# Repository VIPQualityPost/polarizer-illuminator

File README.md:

# Polarizer-Illuminator

A microscope illuminator that includes a liquid crystal display as a tunable polarizer. By polarizing the illuminator light, the reflected light can be filtered through a second polarizer (in this case the LCD) with specular reflections and glare removed, depending on the amount of polarization applied (based on bias across LCD). The illuminator is powered over USB PD and can be controlled via a PC for automated control in conjunctions with motorized XY stages and microscope camera. Firmware can be updated over same cable providing power thanks to DFU bootloader, just hold the button on the back and plug into a PC. 

| Non-polarized image | Polarized image |
| --- | --- |
|  |  |

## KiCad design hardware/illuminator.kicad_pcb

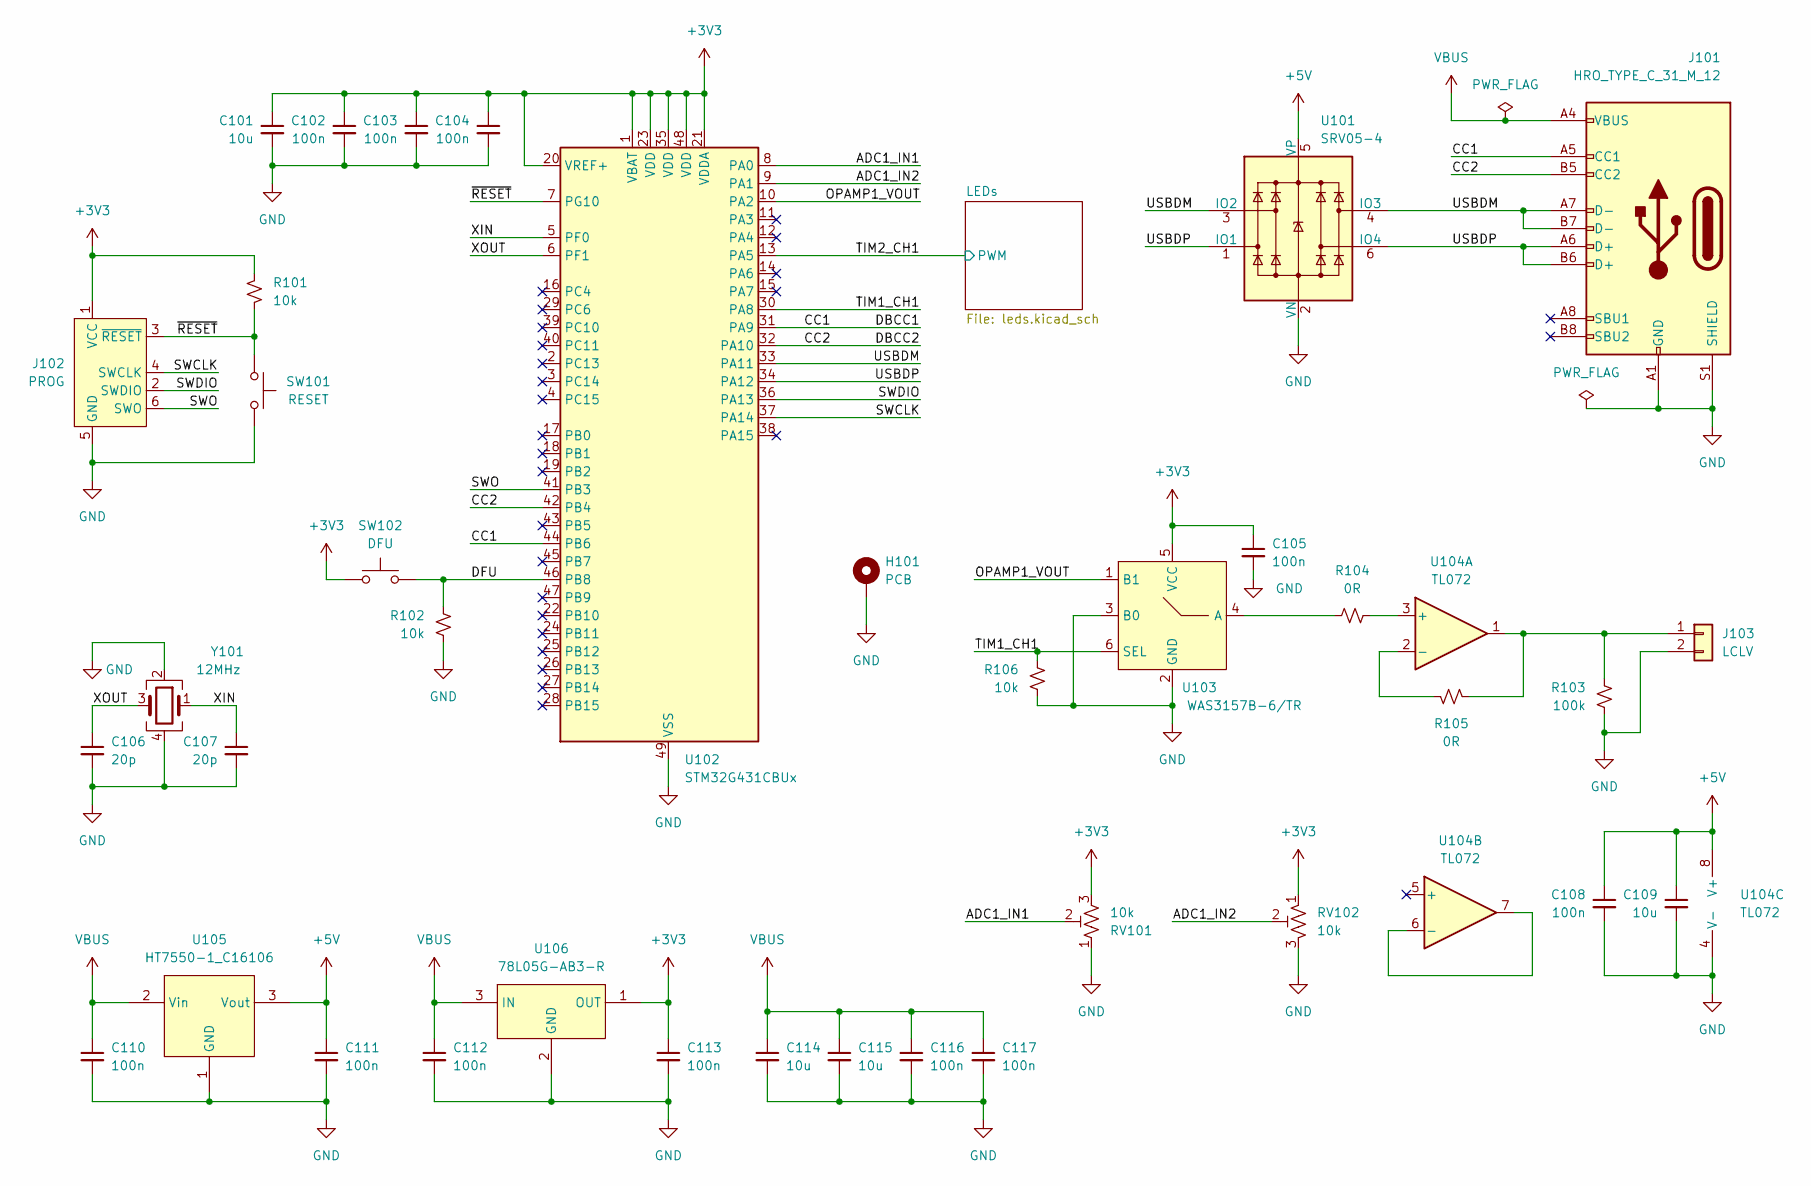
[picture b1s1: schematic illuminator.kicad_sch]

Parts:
C101, C109, C114, C115: 10u; C_0805_2012Metric; LCSC ID C440198
C102, C103, C104, C105, C108, C110, C111, C112, C113, C116, C117: 100n; C_0402_1005Metric; LCSC ID C307331
C106, C107: 20p; C_0402_1005Metric; LCSC ID C1554
H101: PCB; illuminator-monobody
J101: HRO_TYPE_C_31_M_12; USB_C_Receptacle_HRO_TYPE-C-31-M-12; LCSC ID C165948
J102: PROG; Tag-Connect_TC2030-IDC-NL_2x03_P1.27mm_Vertical
J103: LCLV; TestPoint_2Pads_Pitch5.08mm_Drill1.3mm
R101, R102, R106: 10k; R_0402_1005Metric; LCSC ID C25744
R103: 100k; R_0402_1005Metric; LCSC ID C25741
R104, R105: 0R; R_0402_1005Metric; LCSC ID C17168
RV101, RV102: 10k; RES-TH_RK09K1110A0J; LCSC ID C209767
SW101: RESET; PinHeader_1x02_P1.27mm_Vertical
SW102: DFU; KEY-TH_SKHHLWA010; LCSC ID C139764
U101: SRV05-4; SOT-23-6; LCSC ID C7420376
U102: STM32G431CBUx; QFN-48-1EP_7x7mm_P0.5mm_EP5.6x5.6mm; LCSC ID C529356
U103: WAS3157B-6/TR; SOT-363_L2.0-W1.3-P0.65-LS2.1-BL; LCSC ID C213161
U104: TL072; SOIC-8_3.9x4.9mm_P1.27mm; LCSC ID C6961
U105: HT7550-1_C16106; SOT-89-3; LCSC ID C16106
U106: 78L05G-AB3-R; SOT-89-3; LCSC ID C71136
Y101: 12MHz; Crystal_SMD_3225-4Pin_3.2x2.5mm; LCSC ID C9002

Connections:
+3V3: C101.1, C102.1, C103.1, C104.1, C105.1, C113.1, J102.1 (VCC), R101.1, RV101.3, RV102.1, SW102.1, U102.1 (VBAT), U102.20 (VREF+), U102.21 (VDDA), U102.23 (VDD), U102.35 (VDD), U102.48 (VDD), U103.5 (VCC), U106.1 (OUT)
+5V: C108.1, C109.1, C111.1, U101.5 (VP), U104.8 (V+), U105.3 (Vout)
/ADC1_IN1: RV101.2, U102.8 (PA0)
/ADC1_IN2: RV102.2, U102.9 (PA1)
/CC1: J101.A5 (CC1), U102.31 (PA9), U102.44 (PB6)
/CC2: J101.B5 (CC2), U102.32 (PA10), U102.42 (PB4)
/DFU: R102.1, SW102.2, U102.46 (PB8)
/OPAMP1_VOUT: U102.10 (PA2), U103.1 (B1)
/SWCLK: J102.4 (SWCLK), U102.37 (PA14)
/SWDIO: J102.2 (SWDIO), U102.36 (PA13)
/SWO: J102.6 (SWO), U102.41 (PB3)
/TIM1_CH1: R106.1, U102.30 (PA8), U103.6 (SEL)
/TIM2_CH1: U102.13 (PA5); also elsewhere on the board
/USBDM: J101.A7 (D-), J101.B7 (D-), U101.3 (IO2), U101.4 (IO3), U102.33 (PA11)
/USBDP: J101.A6 (D+), J101.B6 (D+), U101.1 (IO1), U101.6 (IO4), U102.34 (PA12)
/XIN: C107.1, U102.5 (PF0), Y101.1
/XOUT: C106.1, U102.6 (PF1), Y101.3
/~RESET: J102.3 (~RESET), R101.2, SW101.2, U102.7 (PG10)
GND: C101.2, C102.2, C103.2, C104.2, C105.2, C106.2, C107.2, C108.2, C109.2, C110.2, C111.2, C112.2, C113.2, C114.2, C115.2, C116.2, C117.2, H101.1, J101.A1 (GND), J101.A12 (GND), J101.B1 (GND), J101.B12 (GND), J101.S1 (SHIELD), J102.5 (GND), J103.2, R102.2, R103.2, R106.2, RV101.1, RV102.3, SW101.1, U101.2 (VN), U102.49 (VSS), U103.2 (GND), U103.3 (B0), U104.4 (V-), U105.1 (GND), U106.2 (GND), Y101.2, Y101.4; also elsewhere on the board
unnamed: J103.1, R103.1, R105.2, U104.1
unnamed: R104.1, U103.4 (A)
unnamed: R104.2, U104.3 (+)
unnamed: R105.1, U104.2 (-)
unnamed: U104.6 (-), U104.7
VBUS: C110.1, C112.1, C114.1, C115.1, C116.1, C117.1, J101.A4 (VBUS), J101.A9 (VBUS), J101.B4 (VBUS), J101.B9 (VBUS), U105.2 (Vin), U106.3 (IN); also elsewhere on the board

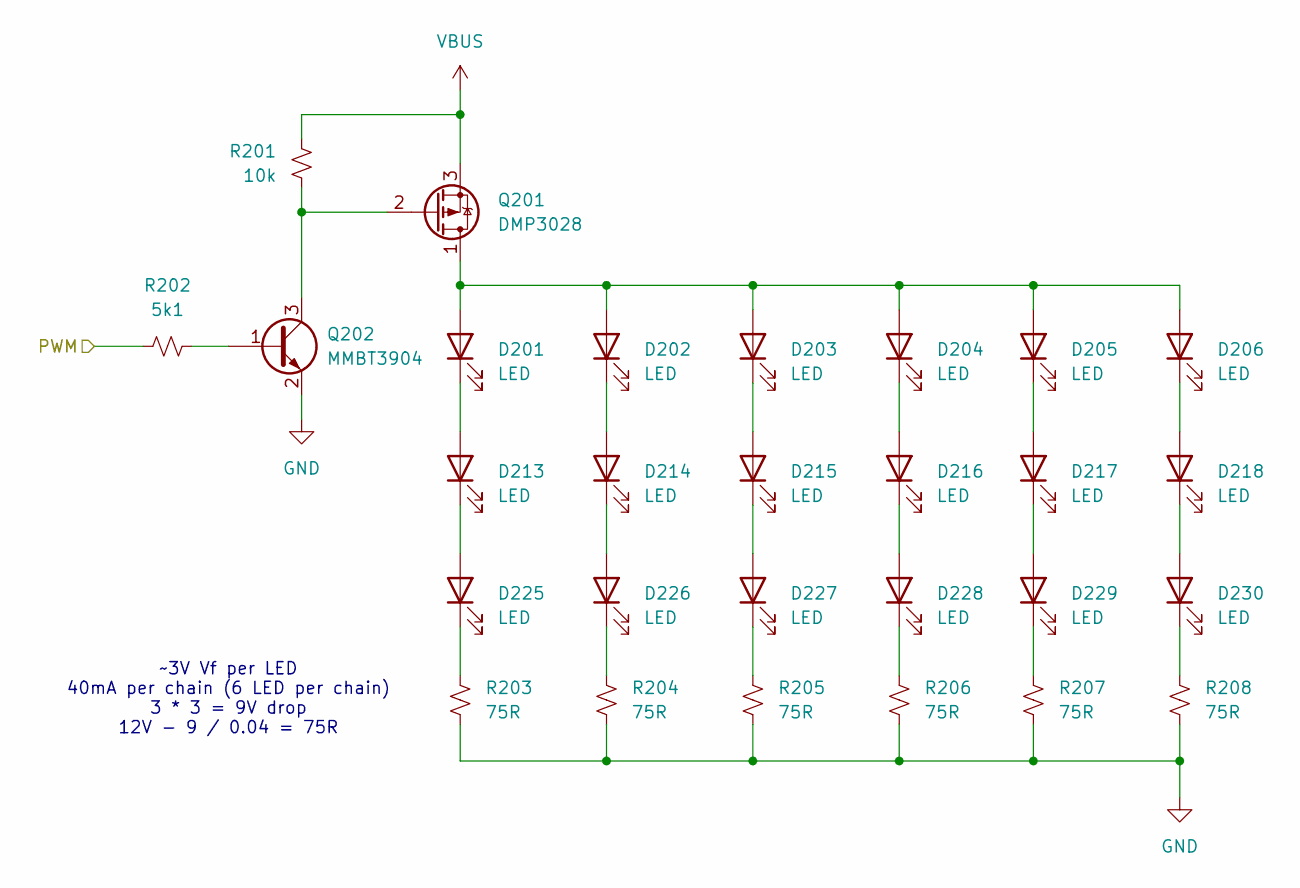
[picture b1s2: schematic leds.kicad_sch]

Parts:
D201, D202, D203, D204, D205, D206, D213, D214, D215, D216, D217, D218, D225, D226, D227, D228, D229, D230: LED; LED_PLCC_2835; LCSC ID C210312
Q201: DMP3028; DMP3028-UDFN2020; LCSC ID C150441
Q202: MMBT3904; SOT-23; LCSC ID C20526
R201: 10k; R_0402_1005Metric; LCSC ID C25744
R202: 5k1; R_0402_1005Metric; LCSC ID C25905
R203, R204, R205, R206, R207, R208: 75R; R_0805_2012Metric; LCSC ID C5198289

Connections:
/TIM2_CH1: R202.1; also elsewhere on the board
GND: Q202.2 (E), R203.2, R204.2, R205.2, R206.2, R207.2, R208.2; also elsewhere on the board
unnamed: D201.2 (A), D202.2 (A), D203.2 (A), D204.2 (A), D205.2 (A), D206.2 (A), Q201.1 (D)
unnamed: D201.1 (K), D213.2 (A)
unnamed: D202.1 (K), D214.2 (A)
unnamed: D203.1 (K), D215.2 (A)
unnamed: D204.1 (K), D216.2 (A)
unnamed: D205.1 (K), D217.2 (A)
unnamed: D206.1 (K), D218.2 (A)
unnamed: D213.1 (K), D225.2 (A)
unnamed: D214.1 (K), D226.2 (A)
unnamed: D215.1 (K), D227.2 (A)
unnamed: D216.1 (K), D228.2 (A)
unnamed: D217.1 (K), D229.2 (A)
unnamed: D218.1 (K), D230.2 (A)
unnamed: D225.1 (K), R203.1
unnamed: D226.1 (K), R204.1
unnamed: D227.1 (K), R205.1
unnamed: D228.1 (K), R206.1
unnamed: D229.1 (K), R207.1
unnamed: D230.1 (K), R208.1
unnamed: Q201.2 (G), Q202.3 (C), R201.2
unnamed: Q202.1 (B), R202.2
VBUS: Q201.3 (S), R201.1; also elsewhere on the board

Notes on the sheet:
~3V Vf per LED 40mA per chain (6 LED per chain) 3 * 3 = 9V drop 12V - 9 / 0.04 = 75R

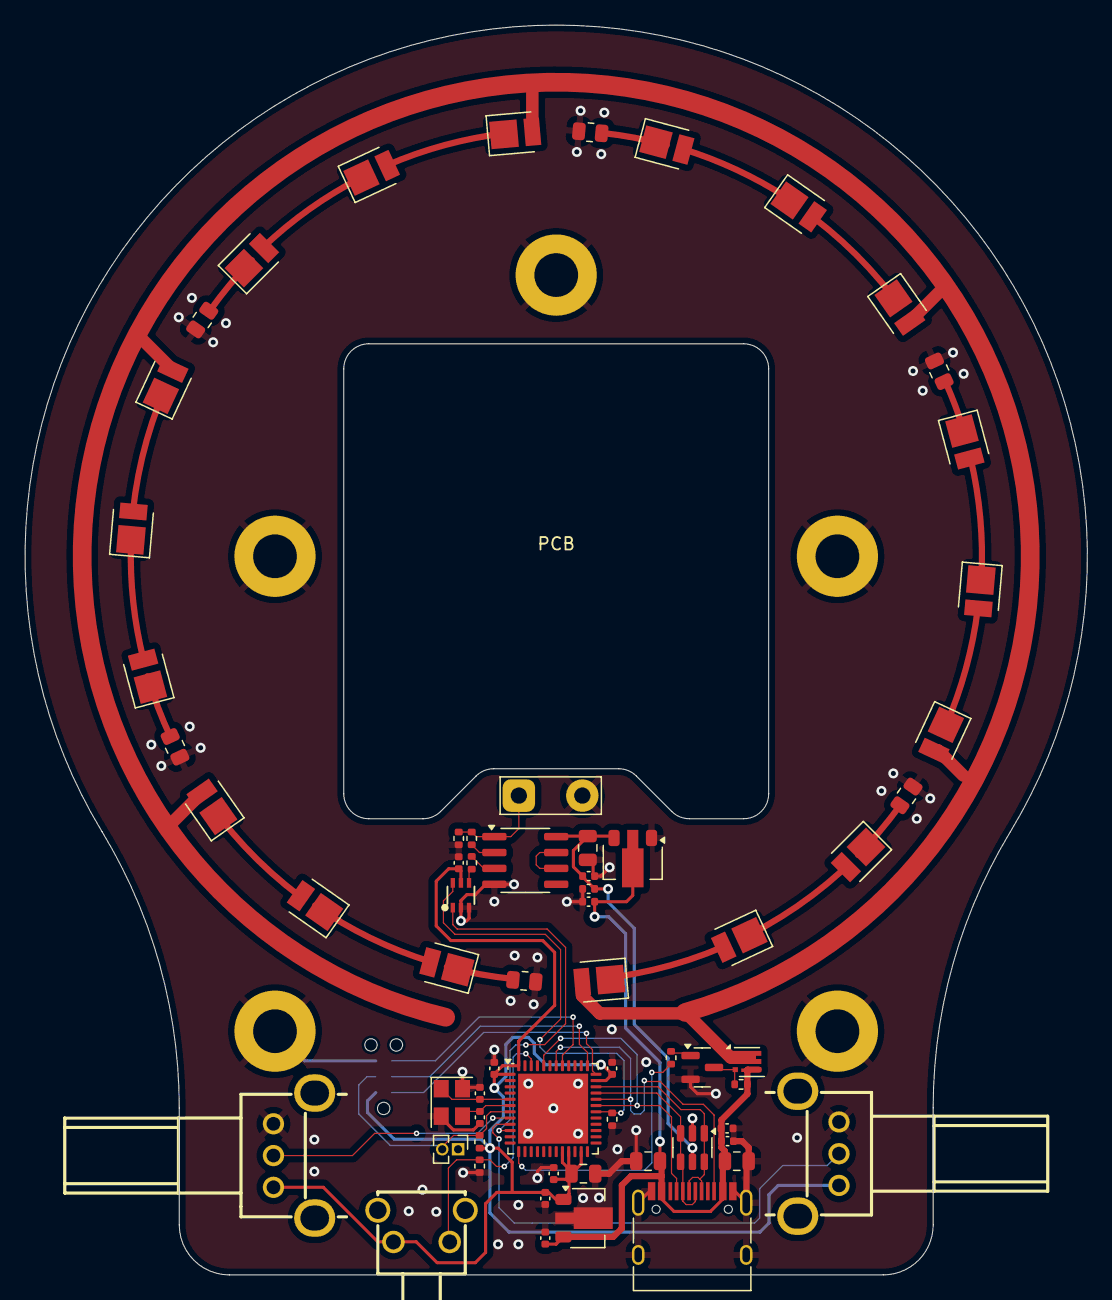
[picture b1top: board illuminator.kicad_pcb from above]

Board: 4 copper layers, 85.0 x 100.0 mm, 66 parts (1 on the bottom side), 46 nets.

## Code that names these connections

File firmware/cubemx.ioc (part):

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Mcu.Name=STM32G431C(6-8-B)Ux
Mcu.Package=UFQFPN48
Mcu.UserName=STM32G431CBUx
PA0.Mode=IN1-Single-Ended
PA0.Signal=ADC1_IN1
PA1.Mode=IN2-Single-Ended
PA1.Signal=ADC1_IN2
PA10.Mode=EnableDeadBattery
PA10.Signal=UCPD1_DBCC2
PA11.Mode=Device
PA11.Signal=USB_DM
PA12.Mode=Device
PA12.Signal=USB_DP
PA13.Mode=Trace_Asynchronous_SW
PA13.Signal=SYS_JTMS-SWDIO
PA14.Mode=Trace_Asynchronous_SW
PA14.Signal=SYS_JTCK-SWCLK
PA2.Mode=Follower-DAC_OUT2-INP
PA2.Signal=OPAMP1_VOUT
PA5.Signal=S_TIM2_CH1
PA8.Signal=S_TIM1_CH1
PA9.Mode=EnableDeadBattery
PA9.Signal=UCPD1_DBCC1
PB3.Mode=Trace_Asynchronous_SW
PB3.Signal=SYS_JTDO-SWO
PB4.Mode=Sink_AllSignals
PB4.Signal=UCPD1_CC2
PB6.Mode=Sink_AllSignals
PB6.Signal=UCPD1_CC1
PF0-OSC_IN.Mode=HSE-External-Oscillator
PF0-OSC_IN.Signal=RCC_OSC_IN
PF1-OSC_OUT.Mode=HSE-External-Oscillator
PF1-OSC_OUT.Signal=RCC_OSC_OUT
RCC.HSE_VALUE=12000000
RCC.SYSCLKFreq_VALUE=168000000
RCC.SYSCLKSource=RCC_SYSCLKSOURCE_PLLCLK
board=custom

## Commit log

2024-03-20 add ci scripts
2024-03-20 restructure
2024-03-20 fix erc errors
2024-03-20 add readme
2024-03-20 Add design file PDFs to repo [skip ci]
2024-03-20 heatsinking
2024-03-20 fix bom
2024-03-20 add gain resistors
2024-03-20 fix drc
2024-03-20 fix zones
2024-03-22 start on fw
2024-03-22 update mechanical design and add tinyusb USB PD
2024-03-23 Update CI and mechanical assembly
2024-03-23 mechanical update
2024-03-31 basic functionality working
2024-03-31 fix dma channel conflict
2024-03-31 get rid of bad submodule
2024-03-31 get LCLV DAC working
2024-03-31 set upload to DFU
2024-03-31 Add missing images
2024-03-31 Fix table in readme
2024-03-31 Fix table... again
2024-04-05 dma working but still crashing
2024-04-23 add cable clamps
2024-04-23 clean up code
2024-04-28 Tidy up
